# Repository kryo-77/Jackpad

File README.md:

# Jackpad
Jackpad is a modular slot machine macropad. Pull the lever and the slots spin and land on a set of macros for an app, either picked at random or chosen by you. Either way, you get the satisfying mechanical spin of a real slot machine.  Snap on extra slots to make it as big as you need.

Made this for https://halflife.hackclub.com/

Slots detaching / attaching:

## Color theme (3d prints):
Retro chrome

Classic casino

## What it is / Why i made it:
- It's a macropad but in a style of a slot machine. The reason I made this is because slot machines look cool and I wanted to combine two completely different things.

## How it works:
- Two PCBs: Main (contains XIAO S3 as the main MCU, only 1 PCB) & Slot (contains ESP32-C3 supermini as the MCU, PCB quantity depends on how many macros you want)
- XIAO S3 acts as a wireless keyboard
- The main pcb has an AS5600 magnetic sensor which is the lever you pull to send signals to the ESP32-C3 for spinning motors.
- ESP32 C3's send signals to XIAO S3 via ESP-NOW (vice-versa) for button presses, motor running etc.
- The slots also have an AS5600 sensor each for positioning the motors correctly so they line the RFID tags correctly.
- Each slot also has a PN532 rfid reader along with small rfid tags which sit on a drum which spin via the motor. A single mechanical switch is present under the drum. PN532 detects a rfid tag which is our 'macro' and as you click on the button, it sends that macro to S3.
- There are limits to how many tags a SLOT can contain (due to size), but no limits to how many SLOT PCBs you can connect with each other, and that too in any order. The slots get a numbering via a 'E-IN / E-OUT' pin on each MCU which does the ordering of slots. A MR30 connector on each pcb has 3 pins: 5v/GND/ENUM for this reason.
- There are two modes: One is just randomly selecting macros, basically a slot machine for looks (though you can set the random macros to do whatever you want). Second mode is where you group different macros together; so like you have macro for music player & 4 slots are connected to main pcb so the macros are: PLAY/PAUSE/NEXT/PREVIOUS. Other group is for FUSION-360 for Sketch/Extrude/Combine/Align tool. So the groups are selected in a sequence; once u pull the lever MUSIC group gets selected, pull lever again Fusion group gets selected and so on (loops), and this is where the AS5600 sensor is most needed.

## UPDATES:
1) Week-1 completed of half-life hackclub.
2) Changed from surface mount components and individual chips to carrier board type mounts for ease of soldering.
3) Completed both main and slot pcb.
4) Completed cad model for main pcb.

## To-do:
1) Work on 3d modeling for week-2 of half-life (slot PCB remaining).

## Project files:

### PCB
1) Folder `kicad_jackpad` contains all the files for PCB/SCHEMATICS for main pcb and slot pcb.
2) Inside is another folder named `breakout_jackpad` which is the main folder. It contains the main pcb files (`breakout_jackpad.pro`) as well as slot pcb files (inside `slot_jackpad` folder).

### CAD

1) Folder `CAD` contains folder `Editable` which has .step & .f3d files for the project.
2) `Printable` contains .stl files.
3) **Notes for printing / editing**
- While viewing / editing file (I used fusion360) models with these prefix in their name need to be:
   - **ig_** : ignored while printing
   - **s_** : separately printed
   - **p_** : printed together (all names with p_ print together even if in different folders)
   - **2p_** : printed together but only with 2p_ in their name (even if in different folders)
   - **3p_**: printed together but only with 3p_ in their name (even if in different folders)

 ### CODE

 Folder `CODE` contains a `main_pcb,ino`.
 It may or may no work and i have no way to test it but as hackclub requires it I did some code for all the components.

 I used AI for AS5600 and MAX98357A as I've never worked with those before

## Jackpad BOM:

NOTE: the quantities are per PCB

| Item | Amount | Cost USD (ea.) | Use | Link |
|------|--------|------------|-----|------|
| 74AHCT125 (DIP-14) + DIP-14 socket | 1 | 0.96 | 3.3V to 5V level shifter for LED data | https://robu.in/product/sn74ahct125n-texas-instruments-8ma-1-4-5v5-5v-8ma-4-dip-14-buffers-drivers-receivers-transceivers-rohs/ |
| MX126-5.0-02P screw terminal | 2 | 0.11 | External 5V input | https://robu.in/product/xy300va-5-0-xinya-2-pin-screw-terminal-blockgreen/ |
| Male pin header strip, 2.54mm (40-pin) | 1 | 0.12 | Headers | https://robu.in/product/2-54mm-2x40-pin-male-double-row-straight-long-header-strip/ |
| Female pin header strip, 2.54mm (40-pin) | 1 | 0.10 | Mount boards | https://robocraze.com/products/40x1-female-berg-strip?_pos=3&_psq=female&_psid=89fdd915c&_ss=e |
| Male to Female jumper wires | 1 | 0.51 | Connect boards | https://robu.in/product/male-to-female-jumper-wires-40-pcs-10cm/ |
| Female to Female jumper wires | 1 | 0.51 | Connect boards | https://robu.in/product/10cm-female-female-breadboard-jumper-dupont-2-54mm-1p-1p-cable-40-pcs/ |
| PN532 RF-ID V3 Module | 1 | 2.68 | RFID reading for macro | https://robocraze.com/products/nfc-near-field-communication-rf-id-v3-module?variant=40193169096857 |
| NFC Tag Sticker \| NTAG213 (pack of 10) | 1 | 1.56 | RFID tags (macros) | https://amzn.in/d/00HLtY3b |
| 0.1uF (100nF) ceramic caps | 10 | 0.10 | Decoupling (1 on main pcb + 2 per slot pcb) | https://robu.in/product/100nf-50v-disc-capacitor/ |
| 1N5819 Schottky diodes | 2 | 0.062 | Power protection for esp32's (1 per board) | https://robu.in/product/1n5819-ap-mcc-40v-1a-600mv1a-do-41-schottky-diodes-rohs/ |
| Electrolytic caps: 470uF x2, 100uF x1, 10uF x1 | 1 | 1.44 | Power smoothing? | https://robu.in/product/aluminum-electrolytic-12-kinds-0-22μf-470μf-capacitor-assorted-kit/ |
| ESP32-C3 SuperMini | 1 | 2.67 | SLOT PCB main board | https://robocraze.com/products/esp32-c3-mini-development-board-unsoldered?variant=48465411506400 |
| Magnetic encoder sensor module AS5600 | 2 | 1.64 | Motor encoder for stopping at soecific points & one for lever | https://robu.in/product/magnetic-encoder-sensor-module-as5600/ |
| DRV8833 motor driver breakout | 1 | 0.75 | Motor control, slot board | https://robocraze.com/products/drv8833-2-channel-dc-motor-driver?variant=46651197784288 |
| N20 600 RPM Motors | 1 | 2.40 | For spinning barrels | https://robocraze.com/products/6v-n20-600-rpm-miniature-gear-motor?variant=41491539886233 |
| MR30 PCB connector (MR30PW-FEMALE, 3-pin) | 2 | 1.03 | Power in/out (1 per slot pcb + 1 in main pcb) | https://partsbaba.com/products/amass-mr30pw30-female-connector-mr30pw-f20-g-y-original-drone-connectors?variant=48877861798045 |
| MR30 PCB connector (MR30PW-MALE, 3-pin) | 2 | 1.14 | Power in/out (1 per slot pcb) | https://partsbaba.com/products/amass-mr30pw30-male-connector-mr30pw-m30-g-y-drone-connectors?variant=48784235626653 |
| MAIN and SLOT PCB ORDER | 2 | 9.30 | PCB manufacture from robu.in | https://robu.in/product/online-pcb-manufacturing-service/ |
| Battery 2500mAh 2S Li-ion | 1 | 5.98 | Power | https://robu.in/product/pro-range-18650-li-ion-2500mah-7-4v-2s1p-protected-battery-pack-3c/ |
| WS2812B LEDs | 6 | 0.05 | Lights | https://robu.in/product/ws2812b-rgb-addressable-led-module/ |
| XIAO S3 | 1 | 11.99 | Main PCB main board | https://robu.in/product/seeed-studio-xiao-esp32s3-2-4ghz-wifi-ble-5-0/ |
| M3 screws | 1 | 3.71 | Screwing printed parts and PCBs together | https://onlyscrews.in/products/m3-allen-button-head-ss304-assorted-box?variant=50368948863289 |
| CAD model print | 1 | 2.50 | 3d print | printing-legion channel |

## Schematics:

### 1) Main PCB

### 2) Slot PCB

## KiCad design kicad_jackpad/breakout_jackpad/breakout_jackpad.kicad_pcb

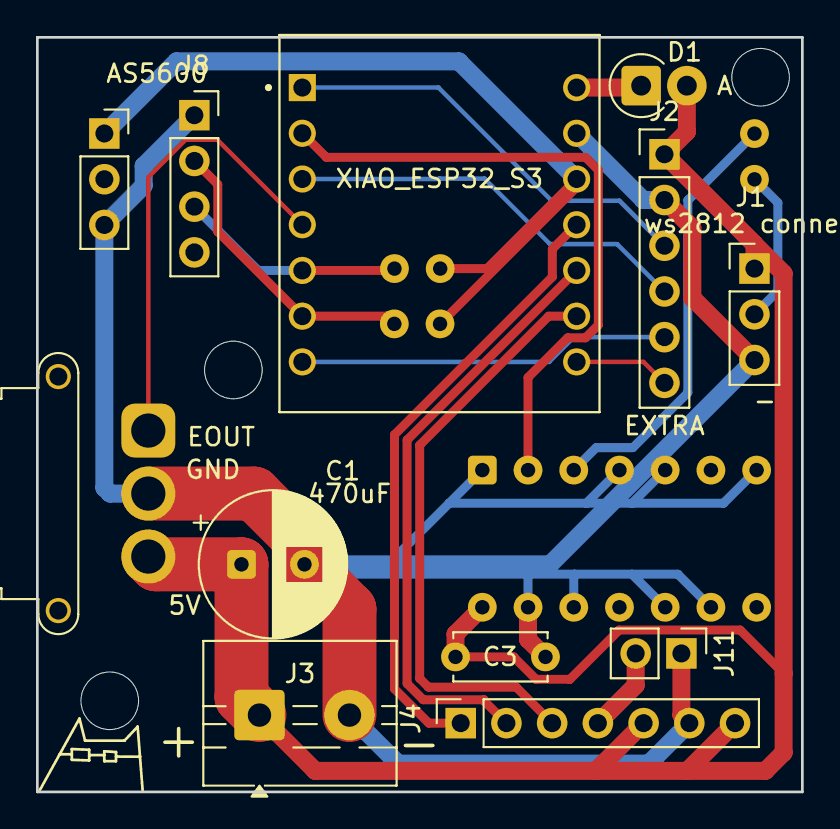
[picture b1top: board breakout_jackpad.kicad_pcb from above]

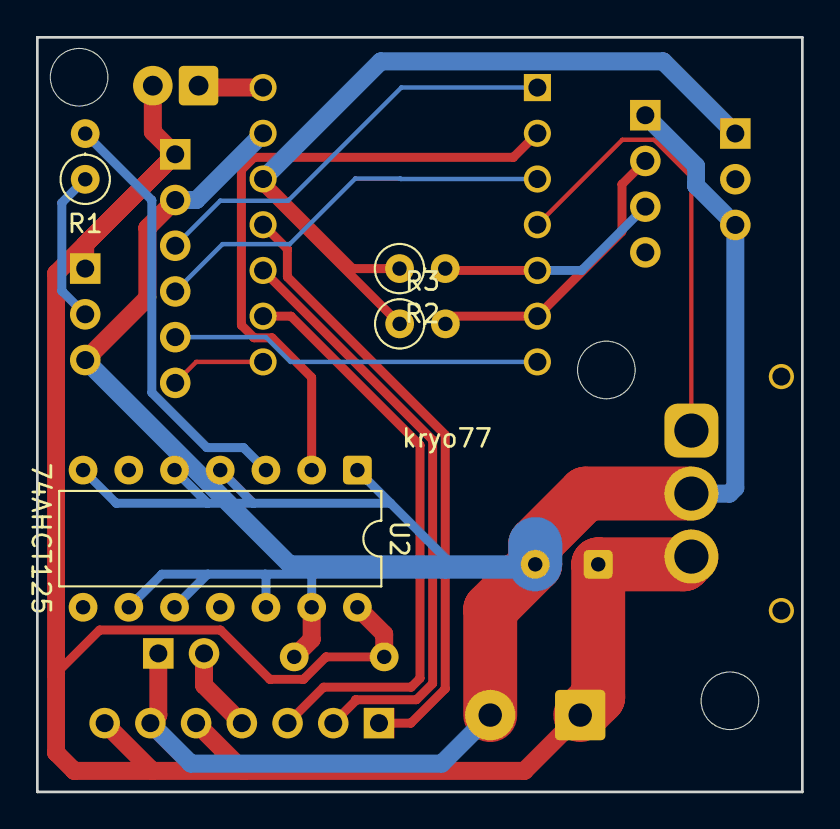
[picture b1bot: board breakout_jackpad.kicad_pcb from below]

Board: 2 copper layers, 42.5 x 41.9 mm, 16 parts (4 on the bottom side), 18 nets.

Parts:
C1: 470uF; CP_Radial_D8.0mm_P3.50mm
C3: 0.1uF; C_Disc_D5.0mm_W2.5mm_P5.00mm
D1: 1N5819; D_DO-41_SOD81_P2.54mm_Vertical_AnodeUp
J1: ws2812 connect; PinHeader_1x03_P2.54mm_Vertical
J2: EXTRA; PinHeader_1x06_P2.54mm_Vertical
J3: Ext 5v supply; TerminalBlock_MaiXu_MX126-5.0-02P_1x02_P5.00mm
J4: MAX98357A; PinSocket_1x07_P2.54mm_Vertical
J8: Conn_01x04_Pin; PinSocket_1x04_P2.54mm_Vertical
J9: Conn_01x03_Pin; PinSocket_1x03_P2.54mm_Vertical
J10: MR30; AMASS_MR30PW-FB_1x03_P3.50mm_Horizontal
J11: jumper cap for 12b; PinHeader_1x02_P2.54mm_Vertical
R1: 330ohm; R_Axial_DIN0207_L6.3mm_D2.5mm_P2.54mm_Vertical
R2, R3: 4.7k; R_Axial_DIN0207_L6.3mm_D2.5mm_P2.54mm_Vertical
U1: XIAO_ESP32_S3; MODULE_XIAO_ESP32_S3
U2: 74AHCT125; DIP-14_W7.62mm

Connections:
+3V3: J9.1 (VCC), R2.1, R3.1, U1.12 (3V3)
+5V: C1.1, C3.2, D1.2 (A), J1.1 (5v), J2.1, J3.1 (OUT+), J4.5 (SD), J4.7 (5v), J10.3 (5V), U2.14 (VCC)
/D0/GPIO1: J2.3, U1.1 (D0/GPIO1)
/D1/GPIO2: U1.2 (D1/GPIO2), U2.2
/D2/GPIO3: J2.4, U1.3 (D2/GPIO3)
/D6/GPIO43: J2.5, U1.7 (D6/GPIO43)
/D7/GPIO44: J2.6, U1.8 (D7/GPIO44)
/D8/GPIO7: J4.3 (DIN), U1.9 (D8/GPIO7)
/D9/GPIO8: J4.2 (BLK), U1.10 (D9/GPIO8)
/D10/GPIO9: J4.1 (LRC), U1.11 (D10/GPIO9)
/ENUM: J10.1 (ENUM), U1.4 (D3/GPIO4)
/SCL: J8.2 (SCL), R3.2, U1.6 (D5/GPIO6)
/SDA: J8.3 (SDA), R2.2, U1.5 (D4/GPIO5)
GND: C1.2, C3.1, J1.3 (GND), J2.2, J3.2 (OUT-), J4.6 (GND), J8.1 (DIR), J9.3 (GND), J10.2 (GND), J11.1, U1.13 (GND), U2.1, U2.4, U2.5, U2.7 (GND), U2.9, U2.10, U2.12, U2.13
unnamed: D1.1 (K), U1.14 (5V)
unnamed: J1.2 (DIN), R1.1
unnamed: J4.4 (GAIN), J11.2
unnamed: R1.2, U2.3

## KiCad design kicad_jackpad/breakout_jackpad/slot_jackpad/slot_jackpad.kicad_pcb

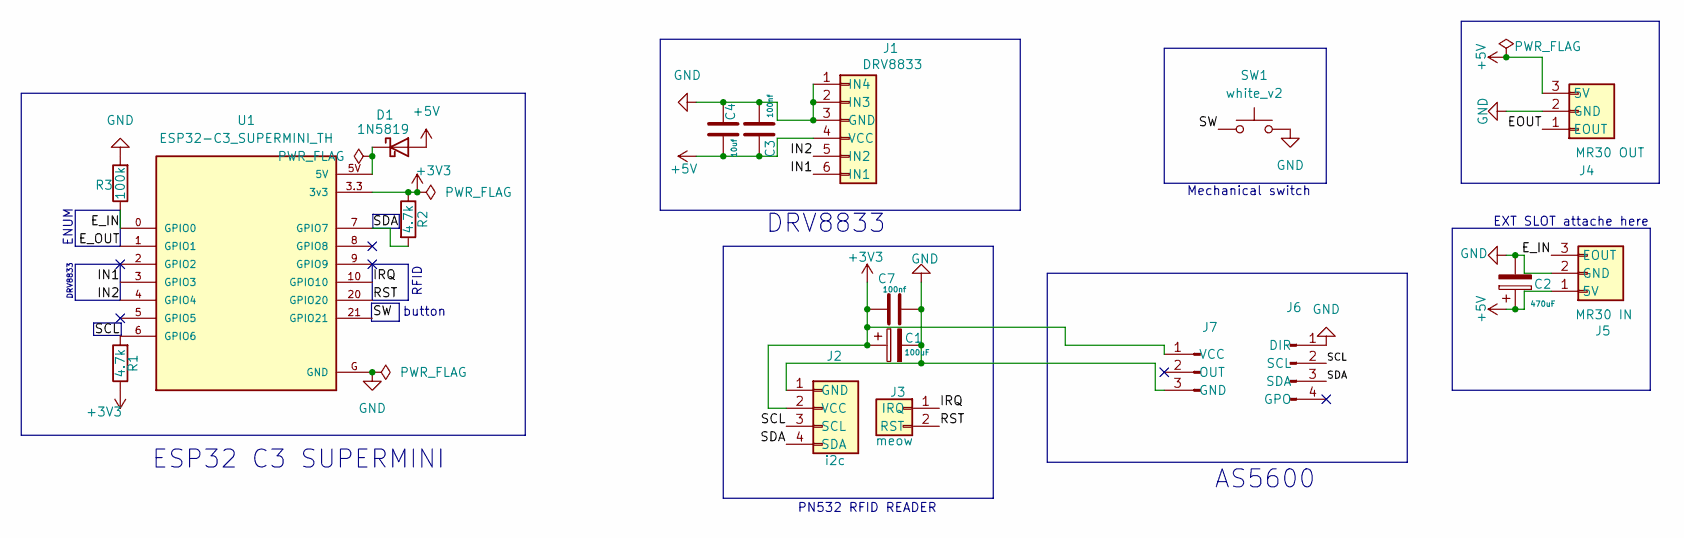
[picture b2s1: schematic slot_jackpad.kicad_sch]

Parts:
C1: 100uF; CP_Radial_D5.0mm_P2.00mm
C2: 470uF; CP_Radial_D8.0mm_P3.50mm
C3, C7: 100nf; C_Disc_D5.0mm_W2.5mm_P5.00mm
C4: 10uf; CP_Radial_D5.0mm_P2.00mm
D1: 1N5819; D_DO-41_SOD81_P2.54mm_Vertical_AnodeUp
J1: DRV8833; PinSocket_1x06_P2.54mm_Vertical
J2: i2c; PinSocket_1x04_P2.54mm_Vertical
J3: meow; PinSocket_1x02_P2.54mm_Vertical
J4: MR30 OUT; AMASS_MR30PW-FB_1x03_P3.50mm_Horizontal
J5: MR30 IN; AMASS_MR30PW-FB_1x03_P3.50mm_Horizontal
J6: Conn_01x04_Pin; PinSocket_1x04_P2.54mm_Vertical
J7: Conn_01x03_Pin; PinSocket_1x03_P2.54mm_Vertical
R1, R2: 4.7k; R_Axial_DIN0207_L6.3mm_D2.5mm_P2.54mm_Vertical
R3: 100k; R_Axial_DIN0207_L6.3mm_D2.5mm_P2.54mm_Vertical
SW1: white_v2; SW_Cherry_MX_1.00u_PCB
U1: ESP32-C3_SUPERMINI_TH; MODULE_ESP32-C3_SUPERMINI_TH

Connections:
+3V3: C1.1, C7.1, J2.2 (VCC), J7.1 (VCC), R1.1, R2.1, U1.3.3 (3v3)
+5V: C2.1, C3.2, C4.1, D1.2 (A), J1.4 (VCC), J4.3 (5V), J5.1 (5V)
/EOUT: J4.1 (EOUT)
/E_IN: J5.3 (EOUT), R3.1, U1.0 (GPIO0)
/E_OUT: U1.1 (GPIO1)
/IN1: J1.6 (IN1), U1.3 (GPIO3)
/IN2: J1.5 (IN2), U1.4 (GPIO4)
/IRQ: J3.1 (IRQ), U1.10 (GPIO10)
/RST: J3.2 (RST), U1.20 (GPIO20)
/SCL: J2.3 (SCL), J6.2 (SCL), R1.2, U1.6 (GPIO6)
/SDA: J2.4 (SDA), J6.3 (SDA), R2.2, U1.7 (GPIO7)
/SW: SW1.1, U1.21 (GPIO21)
GND: C1.2, C2.2, C3.1, C4.2, C7.2, J1.1 (IN4), J1.2 (IN3), J1.3 (GND), J2.1 (GND), J4.2 (GND), J5.2 (GND), J6.1 (DIR), J7.3 (GND), R3.2, SW1.2, U1.G (GND)
unnamed: D1.1 (K), U1.5V

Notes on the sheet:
Mechanical switch
PN532 RFID READER
DRV8833
ESP32 C3 SUPERMINI
button
RFID
AS5600
EXT SLOT attache here
ENUM

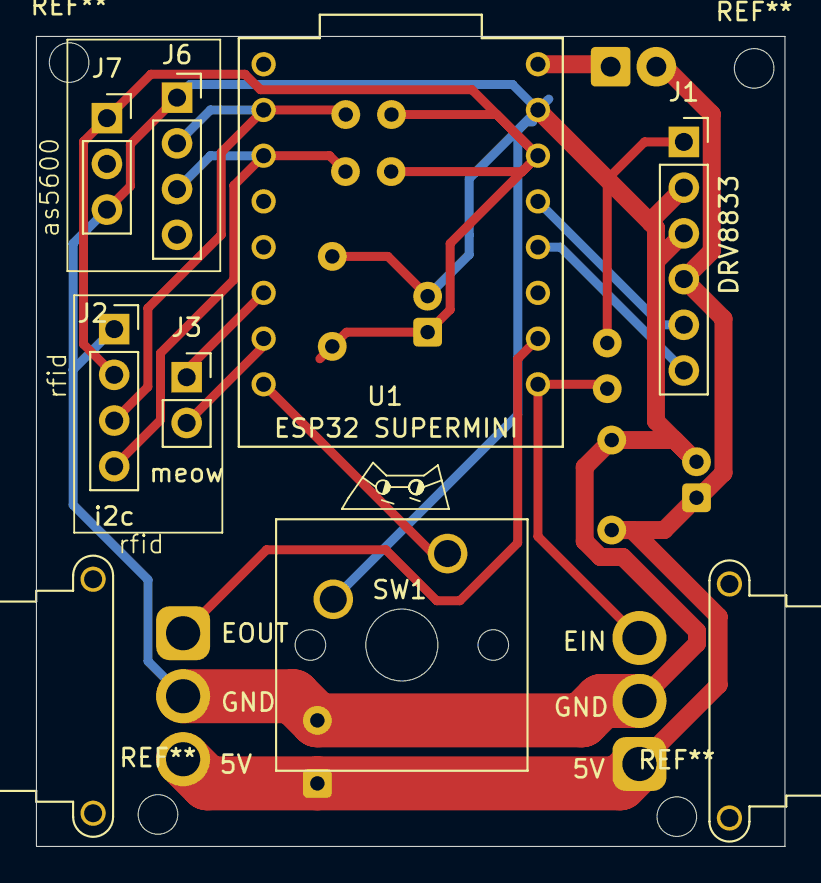
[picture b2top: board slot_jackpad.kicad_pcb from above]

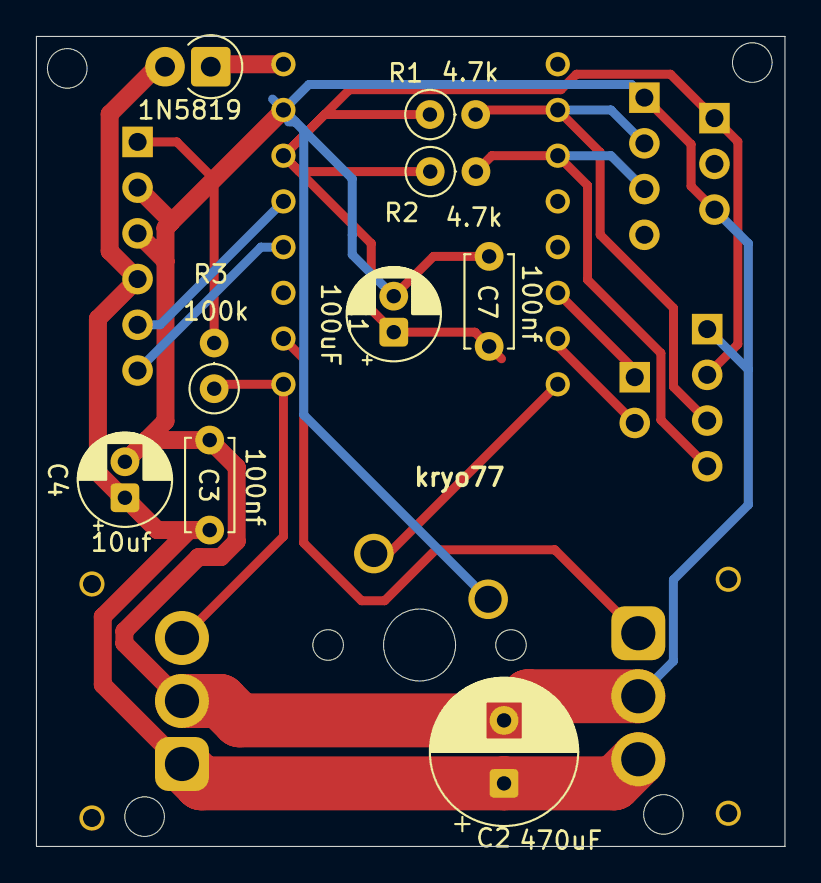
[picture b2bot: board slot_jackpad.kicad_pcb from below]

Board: 2 copper layers, 41.6 x 45.0 mm, 18 parts (9 on the bottom side), 12 nets.

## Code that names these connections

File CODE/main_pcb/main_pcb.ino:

// untested code for main pcb
// Arduino (ESP32 core 3.x)
// Libraries needed: Adafruit NeoPixel
// ESP32 xiao s3
// used ai for as5600 / max98357a beep
#include <Wire.h>
#include <Adafruit_NeoPixel.h>
#include <ESP_I2S.h>

// Pin def
#define LED_PIN    2    // D1/GPIO2 - 74AHCT125 -> WS2812 strip
#define ENUM_PIN   4    // D3/GPIO4 - slot connector J10
#define SDA_PIN    5    // D4/GPIO5 - I2C SDA
#define SCL_PIN    6    // D5/GPIO6 - I2C SCL
#define I2S_DIN    7    // D8/GPIO7 - MAX98357A DIN
#define I2S_BCLK   8    // D9/GPIO8 - MAX98357A BCLK
#define I2S_LRC    9    // D10/GPIO9 - MAX98357A LRC


#define NUM_LEDS     3     // leds present
#define AS5600_ADDR  0x36   // AS5600

Adafruit_NeoPixel strip(NUM_LEDS, LED_PIN, NEO_GRB + NEO_KHZ800);
I2SClass i2s;

// AS5600
int readAngle() {
  Wire.beginTransmission(AS5600_ADDR);
  Wire.write(0x0C);                 // RAW ANGLE register
  if (Wire.endTransmission() != 0) return -1;   // -1 = sensor not found
  Wire.requestFrom(AS5600_ADDR, 2);
  if (Wire.available() < 2) return -1;
  int high = Wire.read();
  int low  = Wire.read();
  return ((high << 8) | low) & 0x0FFF;
}

// beep on amp
void beep(int freq, int ms) {
  const int sampleRate = 16000;
  int samples = sampleRate * ms / 1000;
  for (int i = 0; i < samples; i++) {
  
    int16_t s = ((i * freq * 2 / sampleRate) % 2) ? 3000 : -3000;
    i2s.write((uint8_t*)&s, sizeof(s));
  }
}

void setup() {
  Serial.begin(115200);

  // LEDs
  strip.begin();
  strip.setBrightness(40);   
  strip.show();

  // ENUM 
  pinMode(ENUM_PIN, INPUT_PULLUP);

  // I2C
  Wire.begin(SDA_PIN, SCL_PIN);

  // I2S audio
  i2s.setPins(I2S_BCLK, I2S_LRC, I2S_DIN);
  if (!i2s.begin(I2S_MODE_STD, 16000, I2S_DATA_BIT_WIDTH_16BIT, I2S_SLOT_MODE_MONO)) {
    Serial.println("I2S fail :( )");
  }

  Serial.println("Boot OK");
  beep(880, 200);   // beep beep
}

void loop() {
  //encoder
  int angle = readAngle();

  //slot connector
  bool slotConnected = (digitalRead(ENUM_PIN) == LOW);

  //  Print 
  Serial.printf("angle=%d  slot=%s\n", angle, slotConnected ? "connected" : "empty");

  delay(50);
}
